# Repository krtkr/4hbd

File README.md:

# 4hbd
4 Halfbridge Driver board schematics and PCB files, KiCAD

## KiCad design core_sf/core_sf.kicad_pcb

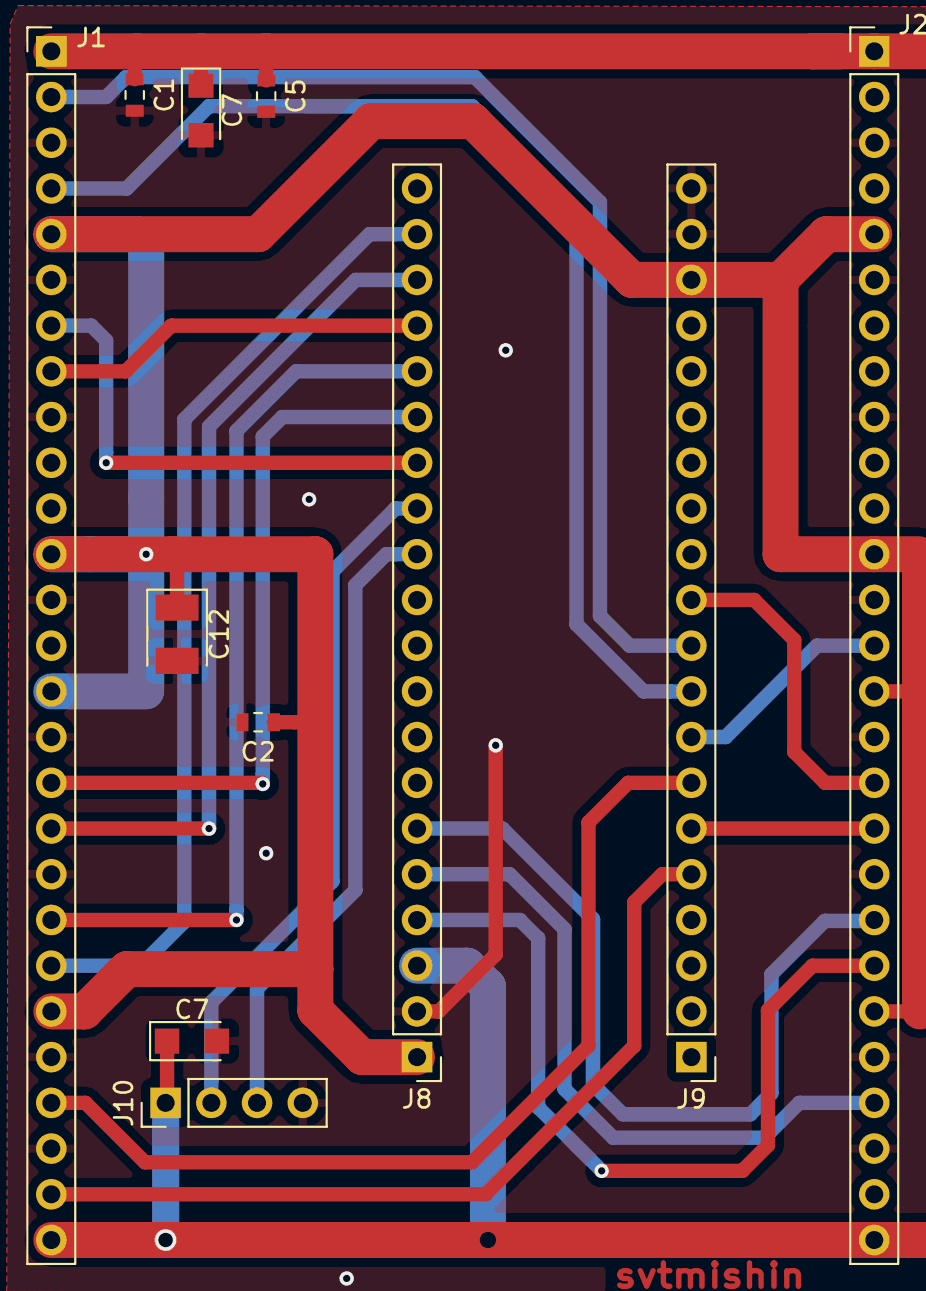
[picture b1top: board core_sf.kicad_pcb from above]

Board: 2 copper layers, 11 parts (0 on the bottom side), 21 nets.

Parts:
C1: 470pF; C_0603_1608Metric
C2, C5: 0.1uF; C_0603_1608Metric
C7, C7#2: 22uF 6.3V; CP_EIA-3216-18_Kemet-A
C12: 220uF 4V; CP_EIA-3528-21_Kemet-B
J1, J2: Conn_01x27; PinHeader_1x27_P2.54mm_Vertical
J8, J9: Conn_01x20; PinHeader_1x20_P2.54mm_Vertical
J10: Conn_01x04; PinHeader_1x04_P2.54mm_Vertical

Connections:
+3V3: C2.1, C12.1, J1.5, J1.12, J1.15, J1.22, J2.5, J2.12, J2.15, J2.22, J8.1, J9.18
+5V: C1.1, C5.1, C7.1, C7#2.1, J1.1, J1.27, J2.1, J2.27, J8.3, J10.1
/ADC1_IN0: J1.4, J9.9
/ADC1_IN3: J2.14, J9.8
/ADC1_IN4: J1.24, J9.7
/ADC2_IN9: J1.26, J9.5
/ADC3_IN10: J1.2, J9.10
/TIM1_CH1: J1.20, J8.16
/TIM1_CH1N: J1.21, J8.19
/TIM1_CH2: J1.17, J8.15
/TIM1_CH2N: J1.18, J8.18
/TIM1_CH4: J1.7, J8.14
/TIM1_CH4N: J1.8, J8.17
/TIM2_FAN_PULSE: J2.18, J9.6
/TIM3_FAN_PWM: J2.17, J9.11
/TIM4_ENC_A: J2.21, J8.4
/TIM4_ENC_B: J2.24, J8.5
/TIM4_ENC_Z: J2.20, J8.6
/canRX: J8.13, J10.2
/canTx: J8.12, J10.3
GND: C1.2, C2.2, C5.2, C7.2, C7#2.2, C12.2, J1.3, J1.6, J1.9, J1.13, J1.16, J1.19, J1.23, J1.25, J2.3, J2.6, J2.9, J2.13, J2.16, J2.19, J2.23, J2.25, J8.2, J9.19, J9.20, J10.4

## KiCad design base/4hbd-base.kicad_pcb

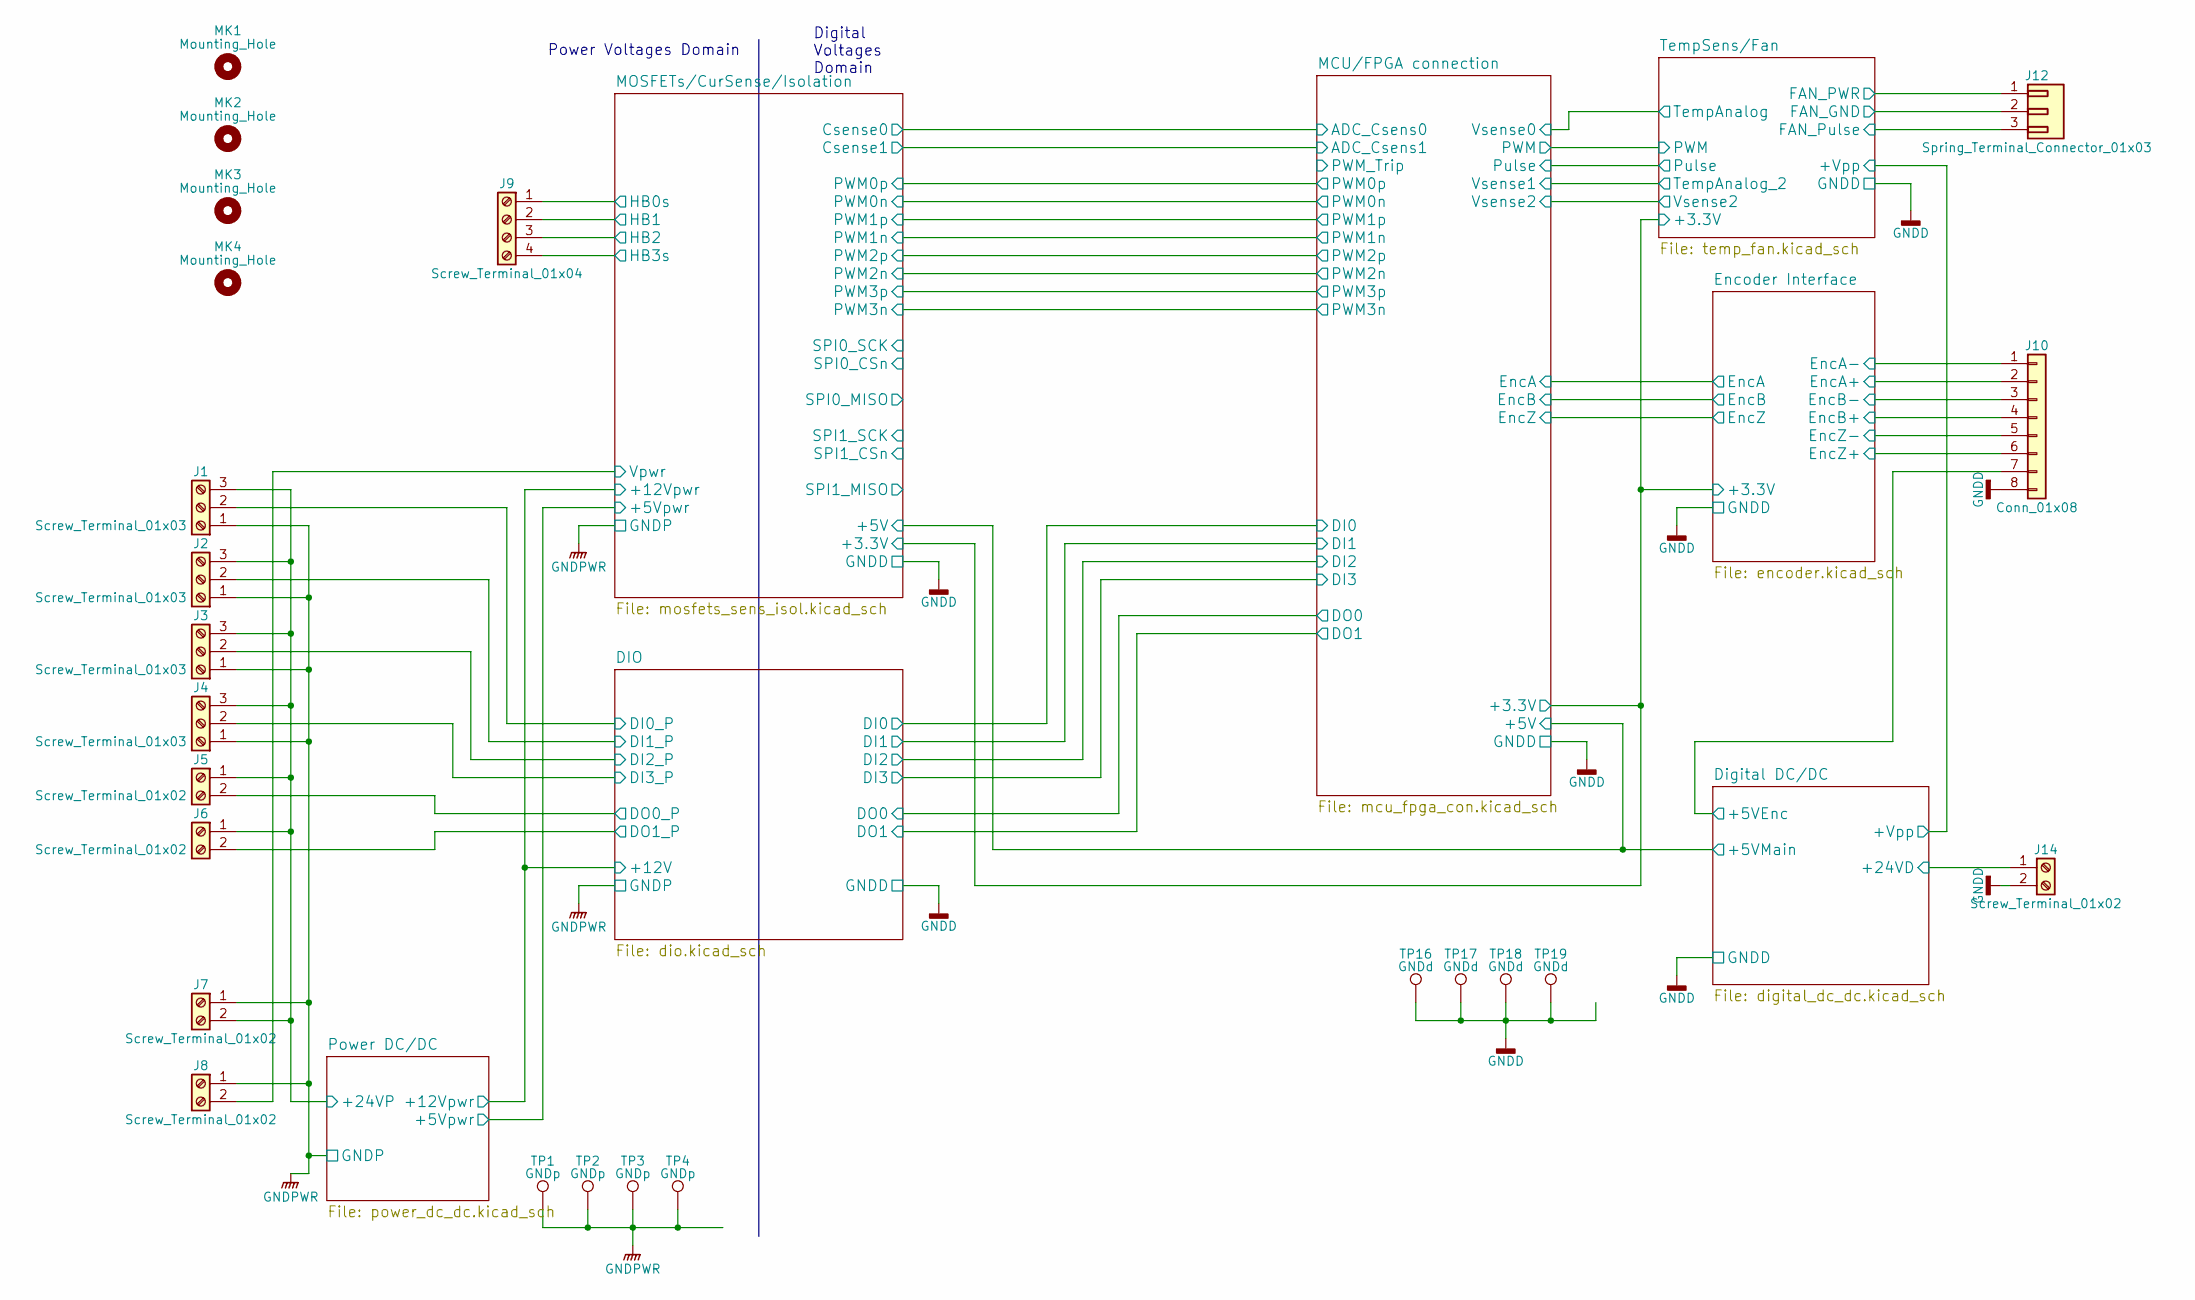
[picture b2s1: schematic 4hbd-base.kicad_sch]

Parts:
J1, J2, J3, J4: Screw_Terminal_01x03; TerminalBlock_Altech_AK300-3_P5.00mm
J5, J6, J7, J8, J14: Screw_Terminal_01x02; TerminalBlock_Altech_AK300-2_P5.00mm
J9: Screw_Terminal_01x04; TerminalBlock_Altech_AK300-4_P5.00mm
J10: Conn_01x08; PinHeader_1x08_P2.54mm_Horizontal
J12: Spring_Terminal_Connector_01x03; PinHeader_1x03_P2.54mm_Vertical
MK1, MK2, MK3, MK4: Mounting_Hole; MountingHole_3.5mm
TP1, TP2, TP3, TP4: GNDp; TestPoint_Pad_D1.5mm
TP16, TP17, TP18, TP19: GNDd; TestPoint_Pad_D1.5mm

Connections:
/DIO/DI0_P: J1.2; also elsewhere on the board
/DIO/DI1_P: J2.2; also elsewhere on the board
/DIO/DI2_P: J3.2; also elsewhere on the board
/DIO/DI3_P: J4.2; also elsewhere on the board
/DIO/DO0_P: J5.2; also elsewhere on the board
/DIO/DO1_P: J6.2; also elsewhere on the board
/Digital DC/DC/+5VEnc: J10.7; also elsewhere on the board
/Digital DC/DC/+24VD: J14.1; also elsewhere on the board
/Encoder Interface/EncA+: J10.2; also elsewhere on the board
/Encoder Interface/EncA-: J10.1; also elsewhere on the board
/Encoder Interface/EncB+: J10.4; also elsewhere on the board
/Encoder Interface/EncB-: J10.3; also elsewhere on the board
/Encoder Interface/EncZ+: J10.6; also elsewhere on the board
/Encoder Interface/EncZ-: J10.5; also elsewhere on the board
/MOSFETs/CurSense/Isolation/HB0s: J9.1; also elsewhere on the board
/MOSFETs/CurSense/Isolation/HB1: J9.2; also elsewhere on the board
/MOSFETs/CurSense/Isolation/HB2: J9.3; also elsewhere on the board
/MOSFETs/CurSense/Isolation/HB3s: J9.4; also elsewhere on the board
/MOSFETs/CurSense/Isolation/Vpwr: J8.2; also elsewhere on the board
/Power DC/DC/+24VP: J1.3, J2.3, J3.3, J4.3, J5.1, J6.1, J7.2; also elsewhere on the board
/TempSens/Fan/FAN_PULSE: J12.3; also elsewhere on the board
/TempSens/Fan/FAN_PWR: J12.1; also elsewhere on the board
GND: J10.8, J12.2, J14.2, TP16.1, TP17.1, TP18.1, TP19.1; also elsewhere on the board
GNDPWR: J1.1, J2.1, J3.1, J4.1, J7.1, J8.1, TP1.1, TP2.1, TP3.1, TP4.1; also elsewhere on the board

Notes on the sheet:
Power Voltages Domain
Digital Voltages Domain

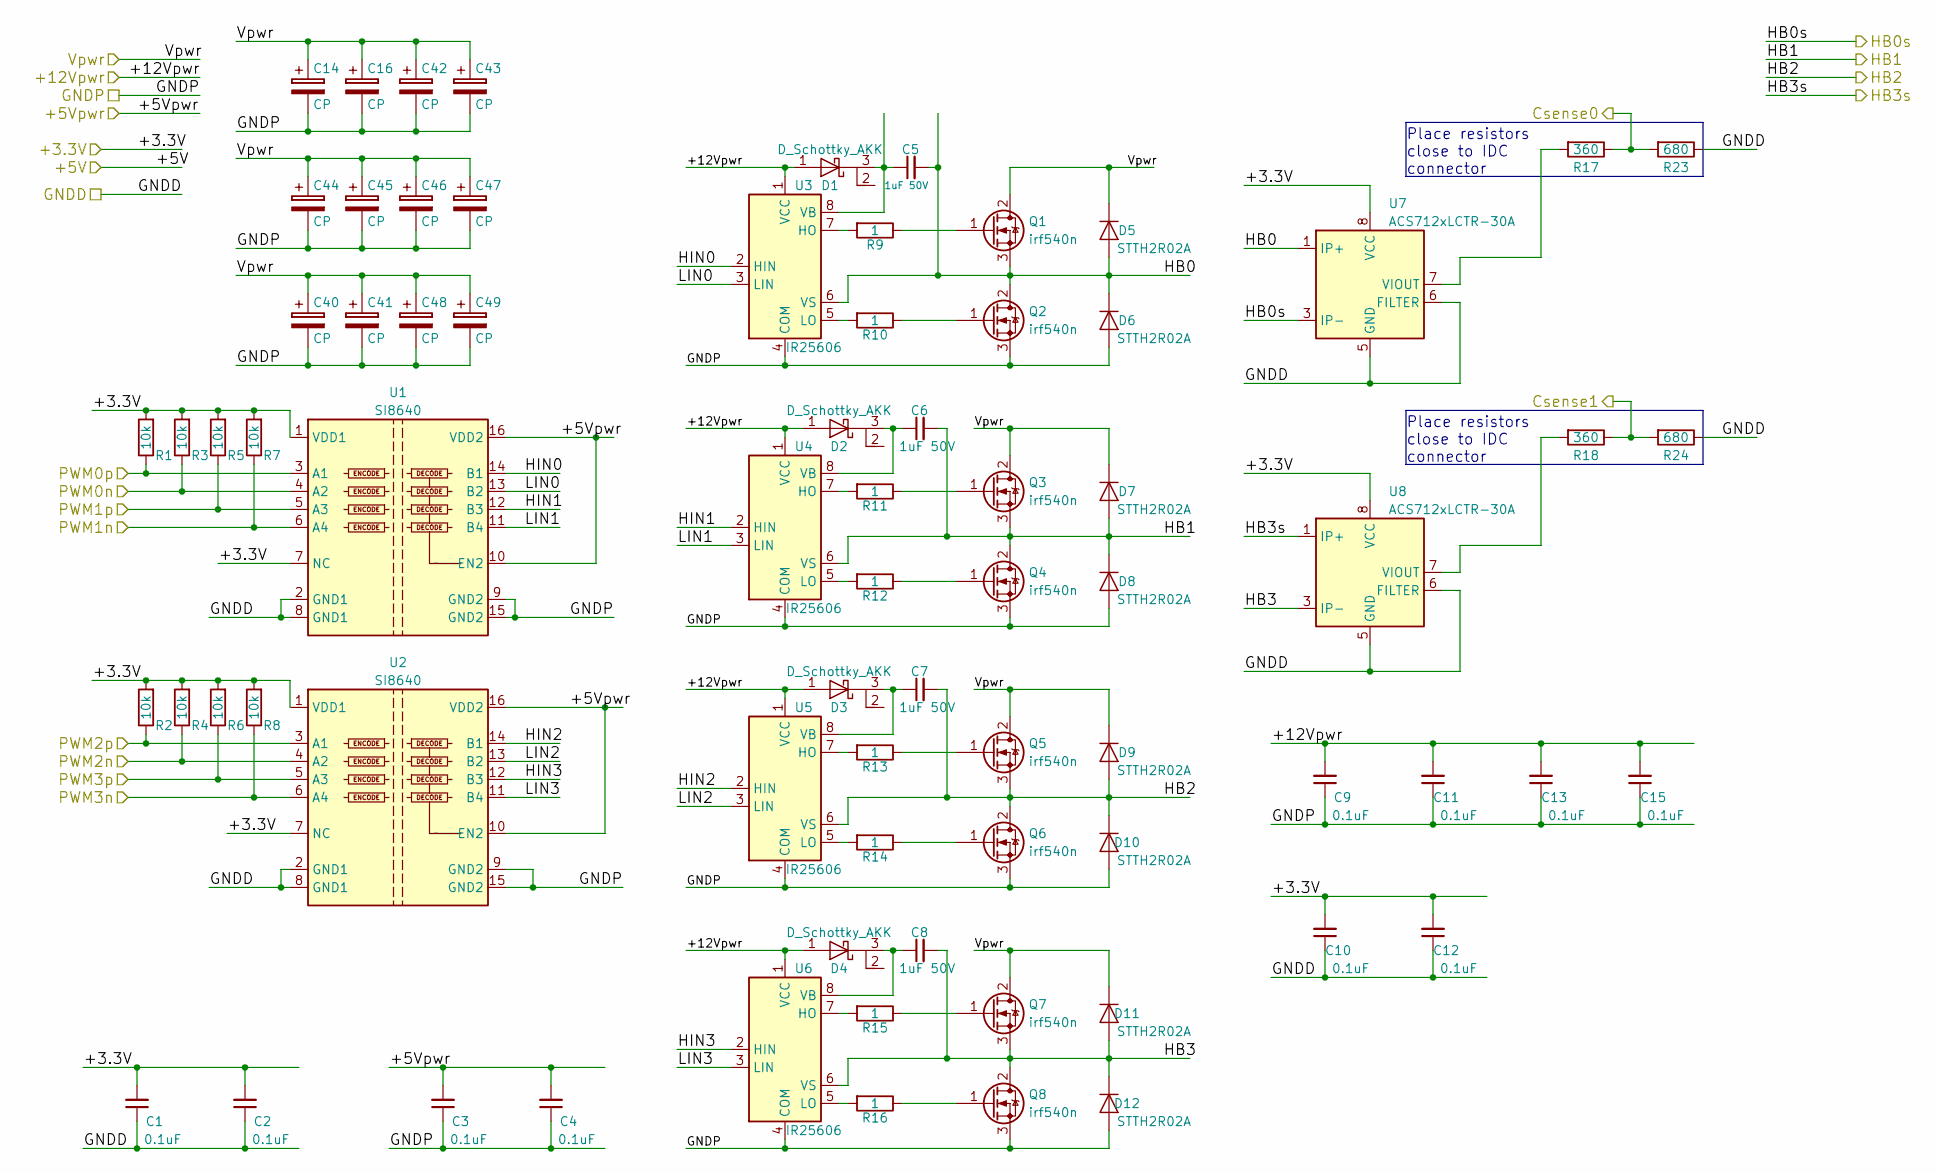
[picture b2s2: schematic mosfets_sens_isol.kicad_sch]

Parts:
C1, C2, C3, C4, C9, C10, C11, C12, C13, C15: 0.1uF; C_0603_1608Metric
C5, C6, C7, C8: 1uF 50V; C_0805_2012Metric
C14, C16: CP; CP_Radial_D22.0mm_P10.00mm_SnapIn
C40, C41, C48, C49: CP; CP_Radial_D10.0mm_P5.00mm
C42, C43: CP; CP_Radial_D12.5mm_P5.00mm
C44, C45, C46, C47: CP; C_2220_5650Metric_Pad2.02x5.50mm_HandSolder
D1, D2, D3, D4: D_Schottky_AKK; SOT-23
D5, D6, D7, D8, D9, D10, D11, D12: STTH2R02A; D_SMA
Q1, Q2, Q3, Q4, Q5, Q6, Q7, Q8: irf540n; TO-220-3_TabUp
R1, R2, R3, R4, R5, R6, R7, R8: 10k; R_0603_1608Metric
R9, R10, R11, R12, R13, R14, R15, R16: 1; R_0603_1608Metric
R17, R18: 360; R_0603_1608Metric
R23, R24: 680; R_0603_1608Metric
U1, U2: SI8640; SOIC-16_3.9x9.9mm_P1.27mm
U3, U4, U5, U6: IR25606; SOIC-8_3.9x4.9mm_P1.27mm
U7, U8: ACS712xLCTR-30A; SOIC-8_3.9x4.9mm_P1.27mm

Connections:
/DIO/+12V: C9.2, C11.2, C13.2, C15.2, D1.1 (A), D2.1 (A), D3.1 (A), D4.1 (A), U3.1 (VCC), U4.1 (VCC), U5.1 (VCC), U6.1 (VCC); also elsewhere on the board
/Encoder Interface/+3.3V: C1.2, C2.2, C10.2, C12.2, R1.2, R2.2, R3.2, R4.2, R5.2, R6.2, R7.2, R8.2, U1.1 (VDD1), U1.7 (NC), U2.1 (VDD1), U2.7 (NC), U7.8 (VCC), U8.8 (VCC); also elsewhere on the board
/MCU/FPGA connection/ADC_Csens0: R17.1, R23.2; also elsewhere on the board
/MCU/FPGA connection/ADC_Csens1: R18.1, R24.2; also elsewhere on the board
/MCU/FPGA connection/PWM0n: R3.1, U1.4 (A2); also elsewhere on the board
/MCU/FPGA connection/PWM0p: R1.1, U1.3 (A1); also elsewhere on the board
/MCU/FPGA connection/PWM1n: R7.1, U1.6 (A4); also elsewhere on the board
/MCU/FPGA connection/PWM1p: R5.1, U1.5 (A3); also elsewhere on the board
/MCU/FPGA connection/PWM2n: R4.1, U2.4 (A2); also elsewhere on the board
/MCU/FPGA connection/PWM2p: R2.1, U2.3 (A1); also elsewhere on the board
/MCU/FPGA connection/PWM3n: R8.1, U2.6 (A4); also elsewhere on the board
/MCU/FPGA connection/PWM3p: R6.1, U2.5 (A3); also elsewhere on the board
/MOSFETs/CurSense/Isolation/+5Vpwr: C3.2, C4.2, U1.10 (EN2), U1.16 (VDD2), U2.10 (EN2), U2.16 (VDD2); also elsewhere on the board
/MOSFETs/CurSense/Isolation/HB0: C5.2, D5.2 (A), D6.1 (K), Q1.3 (S), Q2.2 (D), U3.6 (VS), U7.1 (IP+), U7.2 (IP+)
/MOSFETs/CurSense/Isolation/HB0s: U7.3 (IP-), U7.4 (IP-); also elsewhere on the board
/MOSFETs/CurSense/Isolation/HB1: C6.2, D7.2 (A), D8.1 (K), Q3.3 (S), Q4.2 (D), U4.6 (VS); also elsewhere on the board
/MOSFETs/CurSense/Isolation/HB2: C7.2, D9.2 (A), D10.1 (K), Q5.3 (S), Q6.2 (D), U5.6 (VS); also elsewhere on the board
/MOSFETs/CurSense/Isolation/HB3: C8.2, D11.2 (A), D12.1 (K), Q7.3 (S), Q8.2 (D), U6.6 (VS), U8.3 (IP-), U8.4 (IP-)
/MOSFETs/CurSense/Isolation/HB3s: U8.1 (IP+), U8.2 (IP+); also elsewhere on the board
/MOSFETs/CurSense/Isolation/HIN0: U1.14 (B1), U3.2 (HIN)
/MOSFETs/CurSense/Isolation/HIN1: U1.12 (B3), U4.2 (HIN)
/MOSFETs/CurSense/Isolation/HIN2: U2.14 (B1), U5.2 (HIN)
/MOSFETs/CurSense/Isolation/HIN3: U2.12 (B3), U6.2 (HIN)
/MOSFETs/CurSense/Isolation/LIN0: U1.13 (B2), U3.3 (LIN)
/MOSFETs/CurSense/Isolation/LIN1: U1.11 (B4), U4.3 (LIN)
/MOSFETs/CurSense/Isolation/LIN2: U2.13 (B2), U5.3 (LIN)
/MOSFETs/CurSense/Isolation/LIN3: U2.11 (B4), U6.3 (LIN)
/MOSFETs/CurSense/Isolation/Vpwr: C14.1, C16.1, C40.1, C41.1, C42.1, C43.1, C44.1, C45.1, C46.1, C47.1, C48.1, C49.1, D5.1 (K), D7.1 (K), D9.1 (K), D11.1 (K), Q1.2 (D), Q3.2 (D), Q5.2 (D), Q7.2 (D); also elsewhere on the board
GND: C1.1, C2.1, C10.1, C12.1, R23.1, R24.1, U1.2 (GND1), U1.8 (GND1), U2.2 (GND1), U2.8 (GND1), U7.5 (GND), U7.6 (FILTER), U8.5 (GND), U8.6 (FILTER); also elsewhere on the board
GNDPWR: C3.1, C4.1, C9.1, C11.1, C13.1, C14.2, C15.1, C16.2, C40.2, C41.2, C42.2, C43.2, C44.2, C45.2, C46.2, C47.2, C48.2, C49.2, D6.2 (A), D8.2 (A), D10.2 (A), D12.2 (A), Q2.3 (S), Q4.3 (S), Q6.3 (S), Q8.3 (S), U1.9 (GND2), U1.15 (GND2), U2.9 (GND2), U2.15 (GND2), U3.4 (COM), U4.4 (COM), U5.4 (COM), U6.4 (COM); also elsewhere on the board
unnamed: C5.1, D1.3 (K), U3.8 (VB)
unnamed: C6.1, D2.3 (K), U4.8 (VB)
unnamed: C7.1, D3.3 (K), U5.8 (VB)
unnamed: C8.1, D4.3 (K), U6.8 (VB)
unnamed: Q1.1 (G), R9.1
unnamed: Q2.1 (G), R10.1
unnamed: Q3.1 (G), R11.1
unnamed: Q4.1 (G), R12.1
unnamed: Q5.1 (G), R13.1
unnamed: Q6.1 (G), R14.1
unnamed: Q7.1 (G), R15.1
unnamed: Q8.1 (G), R16.1
unnamed: R9.2, U3.7 (HO)
unnamed: R10.2, U3.5 (LO)
unnamed: R11.2, U4.7 (HO)
unnamed: R12.2, U4.5 (LO)
unnamed: R13.2, U5.7 (HO)
unnamed: R14.2, U5.5 (LO)
unnamed: R15.2, U6.7 (HO)
unnamed: R16.2, U6.5 (LO)
unnamed: R17.2, U7.7 (VIOUT)
unnamed: R18.2, U8.7 (VIOUT)

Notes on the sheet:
Place resistors close to IDC connector

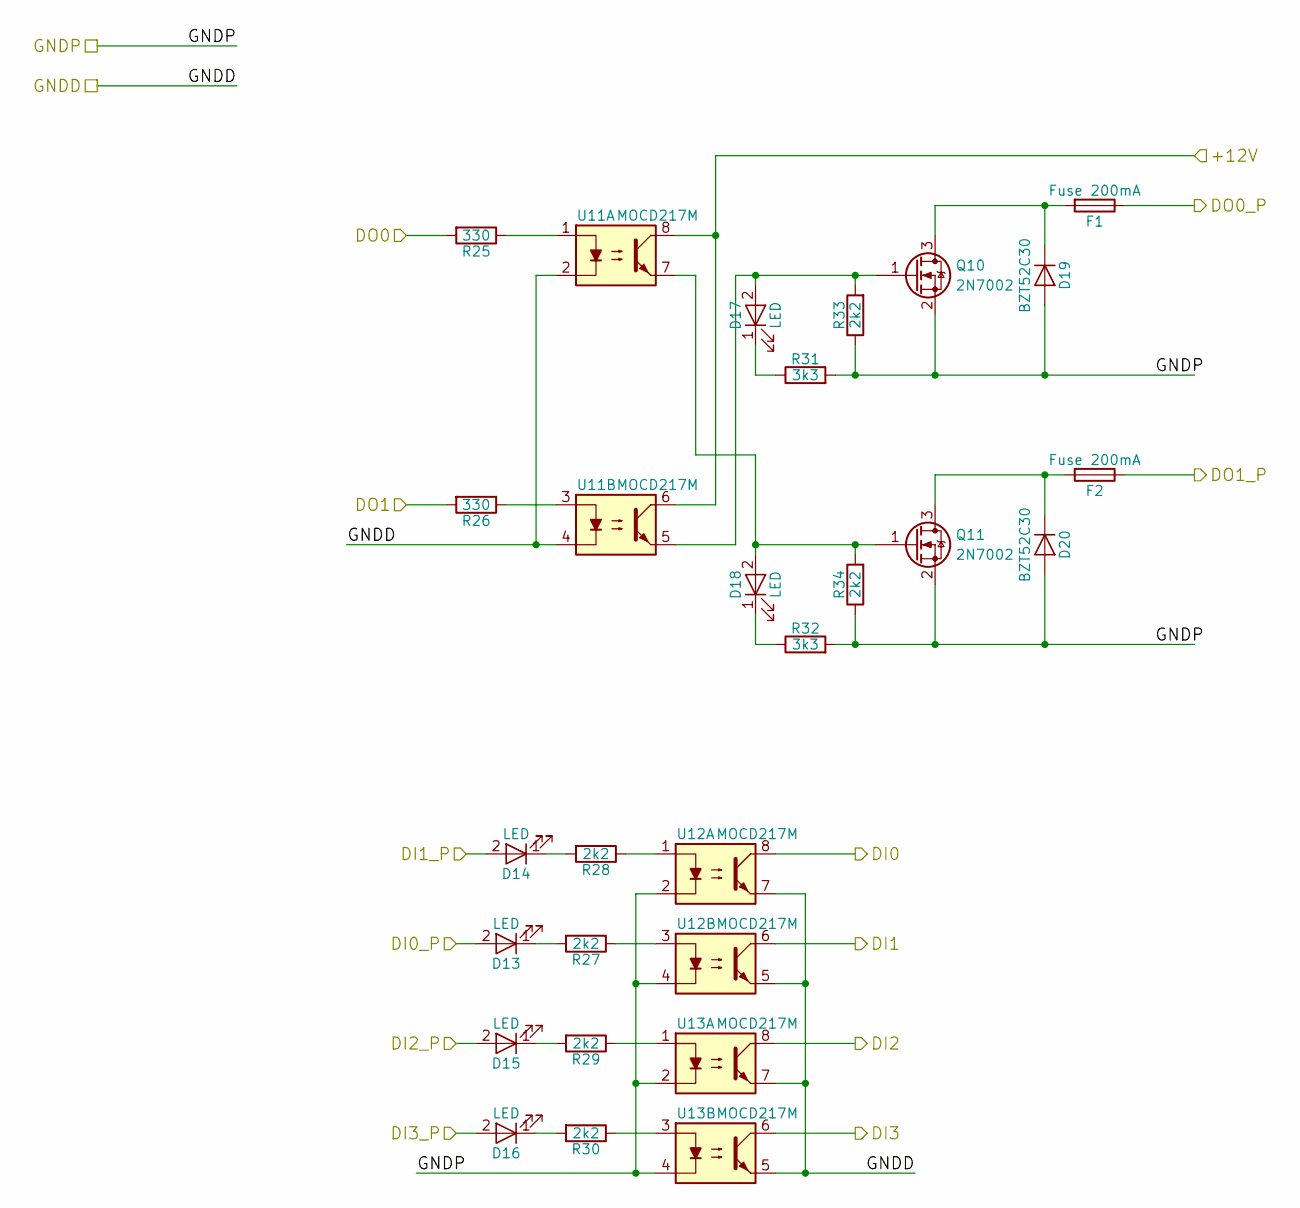
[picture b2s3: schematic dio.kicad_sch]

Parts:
D13, D14, D15, D16, D17, D18: LED; LED_0603_1608Metric_ReverseMount
D19, D20: BZT52C30; D_SOD-123
F1, F2: Fuse 200mA; Fuse_1206_3216Metric
Q10, Q11: 2N7002; SOT-23
R25, R26: 330; R_0603_1608Metric
R27, R28, R29, R30, R33, R34: 2k2; R_0603_1608Metric
R31, R32: 3k3; R_0603_1608Metric
U11, U12, U13: MOCD217M; SOIC-8_3.9x4.9mm_P1.27mm

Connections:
/DIO/+12V: U11.6, U11.8; also elsewhere on the board
/DIO/DI0: U12.8; also elsewhere on the board
/DIO/DI0_P: D13.2 (A); also elsewhere on the board
/DIO/DI1: U12.6; also elsewhere on the board
/DIO/DI1_P: D14.2 (A); also elsewhere on the board
/DIO/DI2: U13.8; also elsewhere on the board
/DIO/DI2_P: D15.2 (A); also elsewhere on the board
/DIO/DI3: U13.6; also elsewhere on the board
/DIO/DI3_P: D16.2 (A); also elsewhere on the board
/DIO/DO0: R25.2; also elsewhere on the board
/DIO/DO0_P: F1.1; also elsewhere on the board
/DIO/DO1: R26.2; also elsewhere on the board
/DIO/DO1_P: F2.1; also elsewhere on the board
GND: U11.2, U11.4, U12.5, U12.7, U13.5, U13.7; also elsewhere on the board
GNDPWR: D19.2 (A), D20.2 (A), Q10.2 (S), Q11.2 (S), R31.2, R32.2, R33.1, R34.1, U12.2, U12.4, U13.2, U13.4; also elsewhere on the board
unnamed: D13.1 (K), R27.2
unnamed: D14.1 (K), R28.2
unnamed: D15.1 (K), R29.2
unnamed: D16.1 (K), R30.2
unnamed: D17.1 (K), R31.1
unnamed: D17.2 (A), Q10.1 (G), R33.2, U11.5
unnamed: D18.1 (K), R32.1
unnamed: D18.2 (A), Q11.1 (G), R34.2, U11.7
unnamed: D19.1 (K), F1.2, Q10.3 (D)
unnamed: D20.1 (K), F2.2, Q11.3 (D)
unnamed: R25.1, U11.1
unnamed: R26.1, U11.3
unnamed: R27.1, U12.3
unnamed: R28.1, U12.1
unnamed: R29.1, U13.1
unnamed: R30.1, U13.3

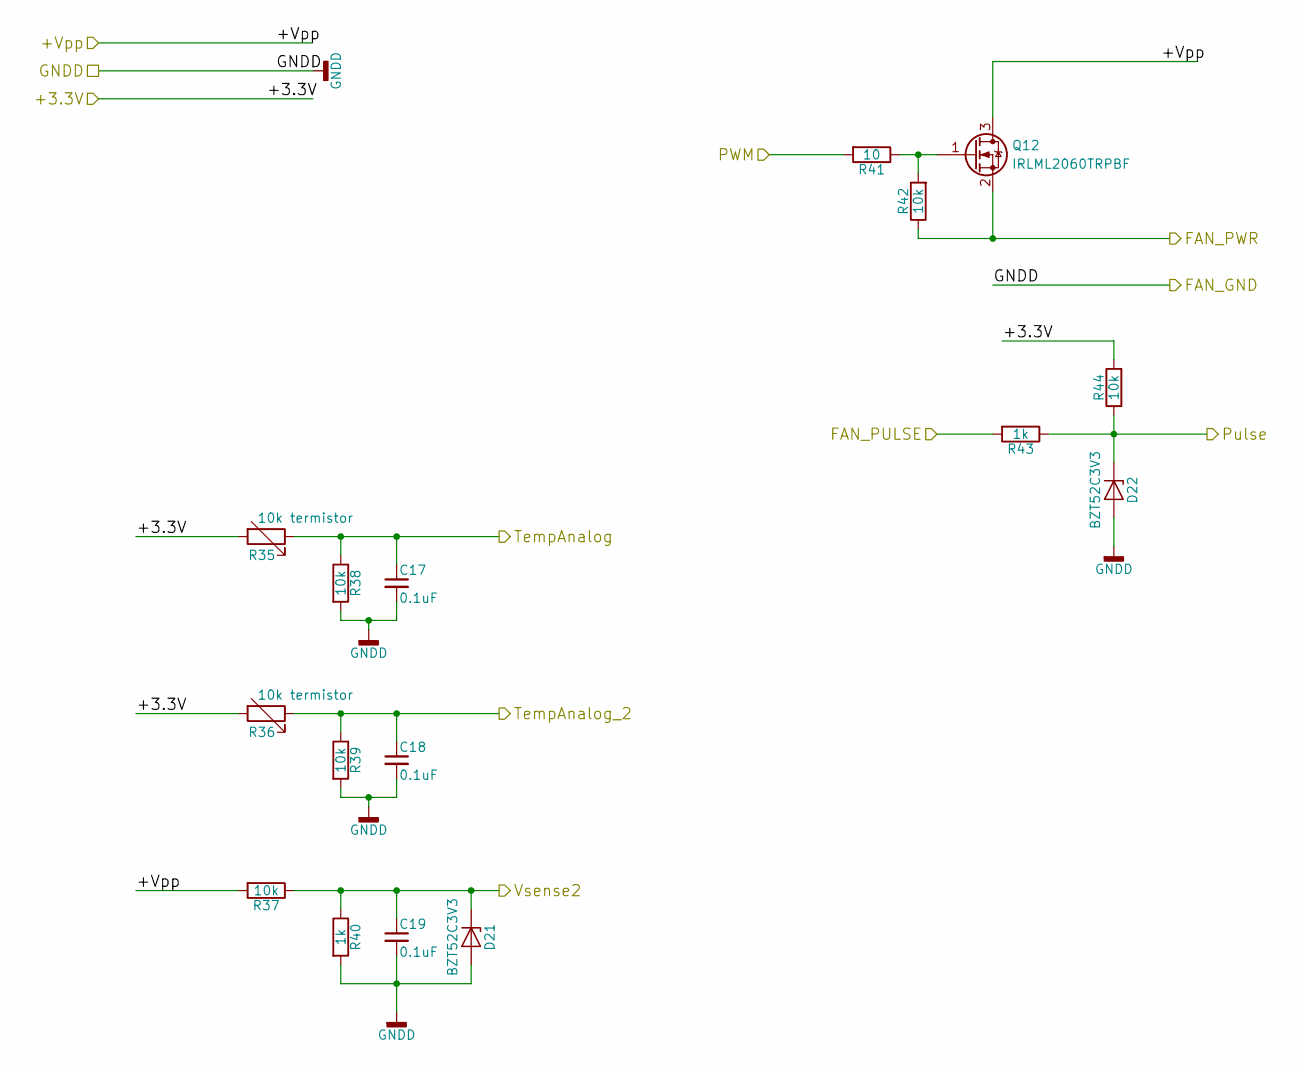
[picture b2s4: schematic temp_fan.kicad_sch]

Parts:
C17, C18, C19: 0.1uF; C_0805_2012Metric
D21, D22: BZT52C3V3; D_SOD-123
Q12: IRLML2060TRPBF; SOT-23
R35, R36: 10k termistor; R_0805_2012Metric
R37, R38, R39, R42, R44: 10k; R_0603_1608Metric
R40, R43: 1k; R_0603_1608Metric
R41: 10; R_0603_1608Metric

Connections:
/Digital DC/DC/+Vpp: Q12.3 (D), R37.2; also elsewhere on the board
/Encoder Interface/+3.3V: R35.2, R36.2, R44.2; also elsewhere on the board
/MCU/FPGA connection/PWM: R41.2; also elsewhere on the board
/MCU/FPGA connection/Pulse: D22.1 (K), R43.1, R44.1; also elsewhere on the board
/MCU/FPGA connection/Vsense2: C19.1, D21.1 (K), R37.1, R40.1; also elsewhere on the board
/TempSens/Fan/FAN_PULSE: R43.2; also elsewhere on the board
/TempSens/Fan/FAN_PWR: Q12.2 (S), R42.1; also elsewhere on the board
/TempSens/Fan/TempAnalog: C17.1, R35.1, R38.1; also elsewhere on the board
/TempSens/Fan/TempAnalog_2: C18.1, R36.1, R39.1; also elsewhere on the board
GND: C17.2, C18.2, C19.2, D21.2 (A), D22.2 (A), R38.2, R39.2, R40.2; also elsewhere on the board
unnamed: Q12.1 (G), R41.1, R42.2

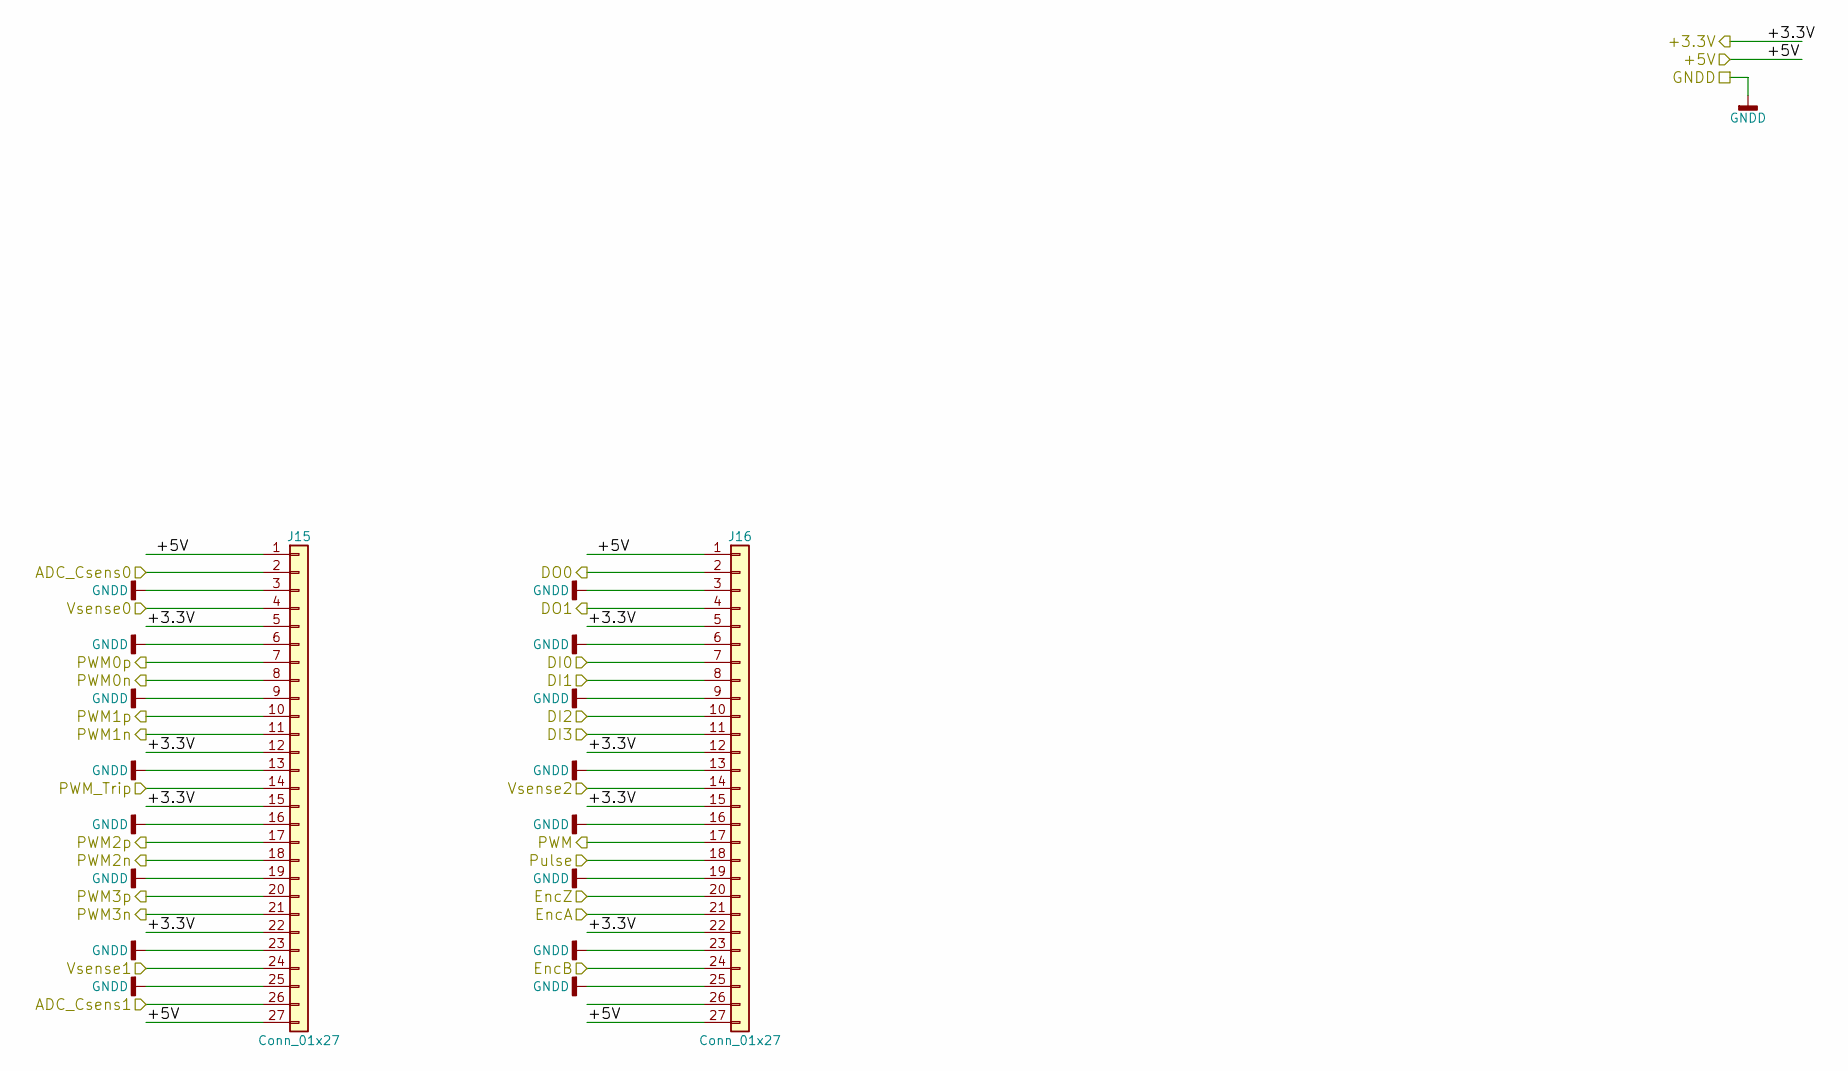
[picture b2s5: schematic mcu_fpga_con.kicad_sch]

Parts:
J15, J16: Conn_01x27; PinHeader_1x27_P2.54mm_Vertical

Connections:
/DIO/DI0: J16.7; also elsewhere on the board
/DIO/DI1: J16.8; also elsewhere on the board
/DIO/DI2: J16.10; also elsewhere on the board
/DIO/DI3: J16.11; also elsewhere on the board
/DIO/DO0: J16.2; also elsewhere on the board
/DIO/DO1: J16.4; also elsewhere on the board
/Encoder Interface/+3.3V: J15.5, J15.12, J15.15, J15.22, J16.5, J16.12, J16.15, J16.22; also elsewhere on the board
/Encoder Interface/EncA: J16.21; also elsewhere on the board
/Encoder Interface/EncB: J16.24; also elsewhere on the board
/Encoder Interface/EncZ: J16.20; also elsewhere on the board
/MCU/FPGA connection/+5V: J15.1, J15.27, J16.1, J16.27; also elsewhere on the board
/MCU/FPGA connection/ADC_Csens0: J15.2; also elsewhere on the board
/MCU/FPGA connection/ADC_Csens1: J15.26; also elsewhere on the board
/MCU/FPGA connection/PWM: J16.17; also elsewhere on the board
/MCU/FPGA connection/PWM0n: J15.8; also elsewhere on the board
/MCU/FPGA connection/PWM0p: J15.7; also elsewhere on the board
/MCU/FPGA connection/PWM1n: J15.11; also elsewhere on the board
/MCU/FPGA connection/PWM1p: J15.10; also elsewhere on the board
/MCU/FPGA connection/PWM2n: J15.18; also elsewhere on the board
/MCU/FPGA connection/PWM2p: J15.17; also elsewhere on the board
/MCU/FPGA connection/PWM3n: J15.21; also elsewhere on the board
/MCU/FPGA connection/PWM3p: J15.20; also elsewhere on the board
/MCU/FPGA connection/Pulse: J16.18; also elsewhere on the board
/MCU/FPGA connection/Vsense2: J16.14; also elsewhere on the board
/TempSens/Fan/TempAnalog: J15.4; also elsewhere on the board
/TempSens/Fan/TempAnalog_2: J15.24; also elsewhere on the board
GND: J15.3, J15.6, J15.9, J15.13, J15.16, J15.19, J15.23, J15.25, J16.3, J16.6, J16.9, J16.13, J16.16, J16.19, J16.23, J16.25; also elsewhere on the board

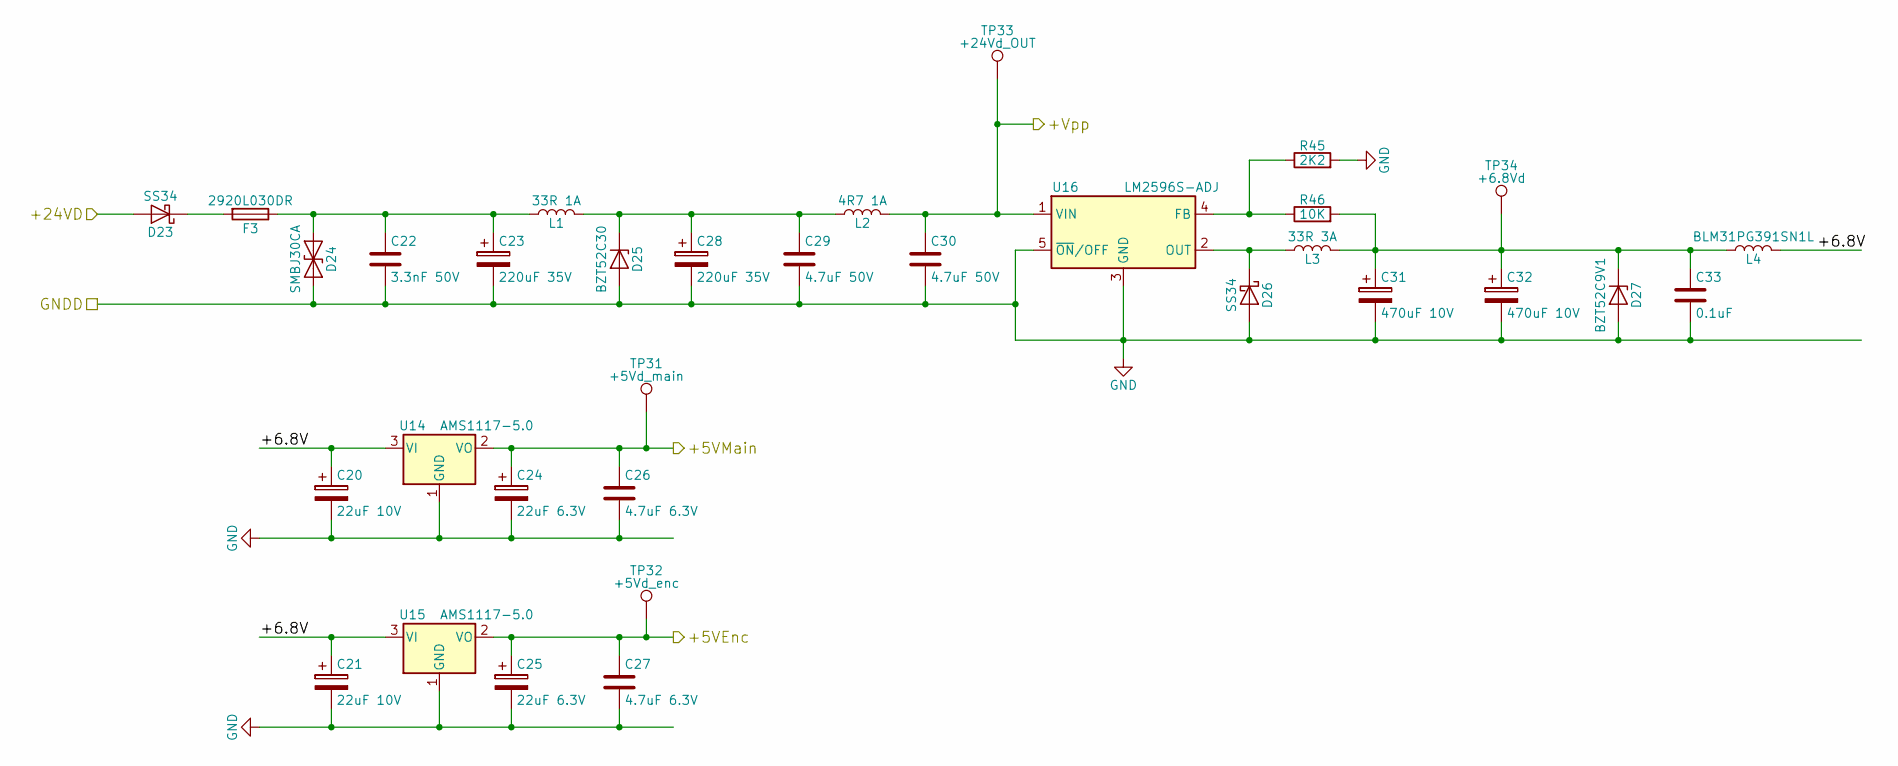
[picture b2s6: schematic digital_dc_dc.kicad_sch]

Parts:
C20, C21: 22uF 10V; CP_EIA-3216-18_Kemet-A
C22: 3.3nF 50V; C_0603_1608Metric
C23, C28: 220uF 35V; CP_Elec_8x10
C24, C25: 22uF 6.3V; CP_EIA-3216-18_Kemet-A
C26, C27: 4.7uF 6.3V; C_0603_1608Metric
C29, C30: 4.7uF 50V; C_1210_3225Metric
C31, C32: 470uF 10V; CP_Elec_8x10
C33: 0.1uF; C_0603_1608Metric
D23, D26: SS34; D_SMA
D24: SMBJ30CA; D_SMB
D25: BZT52C30; D_SOD-123
D27: BZT52C9V1; D_SOD-123
F3: 2920L030DR; Fuse_2920_7451Metric
L1: 33R 1A; L_7.3x7.3_H3.5
L2: 4R7 1A; L_Taiyo-Yuden_MD-3030
L3: 33R 3A; L_12x12mm_h8mm
L4: BLM31PG391SN1L; L_1206_3216Metric
R45: 2K2; R_0603_1608Metric
R46: 10K; R_0603_1608Metric
TP31: +5Vd_main; TestPoint_Pad_D1.5mm
TP32: +5Vd_enc; TestPoint_Pad_D1.5mm
TP33: +24Vd_OUT; TestPoint_Pad_D1.5mm
TP34: +6.8Vd; TestPoint_Pad_D1.5mm
U14, U15: AMS1117-5.0; SOT-223
U16: LM2596S-ADJ; TO-263-5_TabPin3

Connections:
/Digital DC/DC/+5VEnc: C25.1, C27.1, TP32.1, U15.2 (VO), U15.4; also elsewhere on the board
/Digital DC/DC/+6.8V: C20.1, C21.1, L4.2, U14.3 (VI), U15.3 (VI)
/Digital DC/DC/+24VD: D23.2 (A); also elsewhere on the board
/Digital DC/DC/+Vpp: C30.1, L2.2, TP33.1, U16.1 (VIN); also elsewhere on the board
/MCU/FPGA connection/+5V: C24.1, C26.1, TP31.1, U14.2 (VO), U14.4; also elsewhere on the board
GND: C20.2, C21.2, C22.2, C23.2, C24.2, C25.2, C26.2, C27.2, C28.2, C29.2, C30.2, C31.2, C32.2, C33.2, D24.2 (A2), D25.2 (A), D26.2 (A), D27.2 (A), R45.2, U14.1 (GND), U15.1 (GND), U16.3 (GND), U16.5 (~ON/OFF); also elsewhere on the board
unnamed: C22.1, C23.1, D24.1 (A1), F3.1, L1.1
unnamed: C28.1, C29.1, D25.1 (K), L1.2, L2.1
unnamed: C31.1, C32.1, C33.1, D27.1 (K), L3.2, L4.1, R46.2, TP34.1
unnamed: D23.1 (K), F3.2
unnamed: D26.1 (K), L3.1, U16.2 (OUT)
unnamed: R45.1, R46.1, U16.4 (FB)

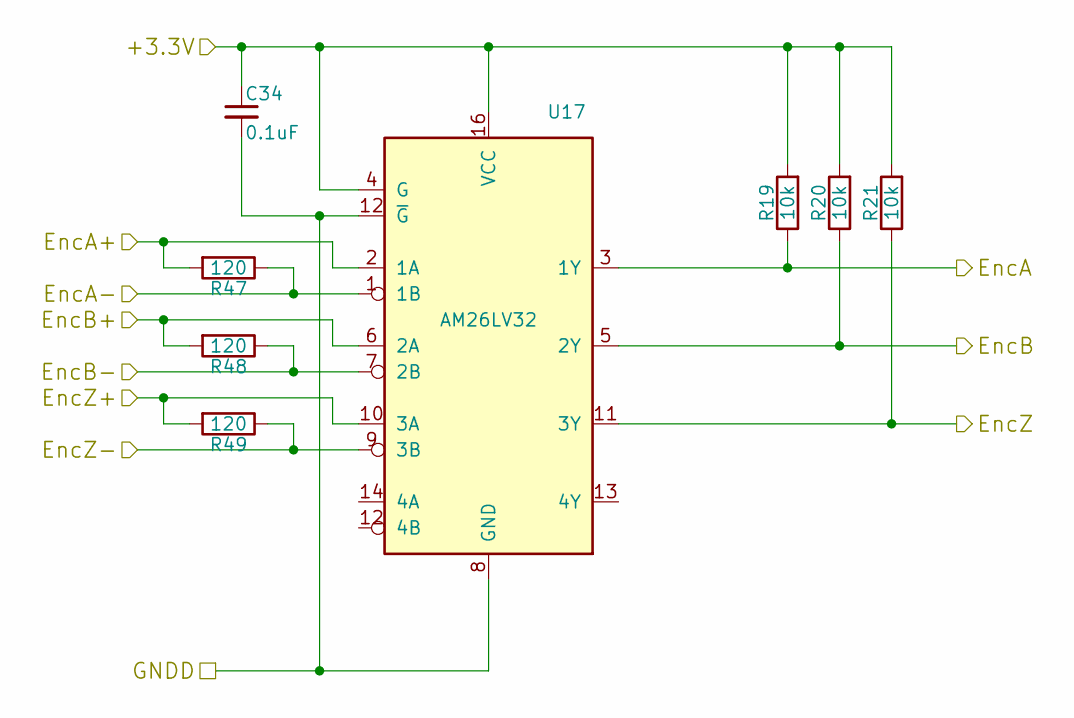
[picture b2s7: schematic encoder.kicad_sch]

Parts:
C34: 0.1uF; C_0603_1608Metric
R19, R20, R21: 10k; R_0603_1608Metric
R47, R48, R49: 120; R_0603_1608Metric
U17: AM26LV32; SOIC-16_3.9x9.9mm_P1.27mm

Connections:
/Encoder Interface/+3.3V: C34.1, R19.2, R20.2, R21.2, U17.4 (G), U17.16 (VCC); also elsewhere on the board
/Encoder Interface/EncA: R19.1, U17.3 (1Y); also elsewhere on the board
/Encoder Interface/EncA+: R47.2, U17.2 (1A); also elsewhere on the board
/Encoder Interface/EncA-: R47.1, U17.1 (1B); also elsewhere on the board
/Encoder Interface/EncB: R20.1, U17.5 (2Y); also elsewhere on the board
/Encoder Interface/EncB+: R48.2, U17.6 (2A); also elsewhere on the board
/Encoder Interface/EncB-: R48.1, U17.7 (2B); also elsewhere on the board
/Encoder Interface/EncZ: R21.1, U17.11 (3Y); also elsewhere on the board
/Encoder Interface/EncZ+: R49.2, U17.10 (3A); also elsewhere on the board
/Encoder Interface/EncZ-: R49.1, U17.9 (3B); also elsewhere on the board
GND: C34.2, U17.8 (GND), U17.12 (4B); also elsewhere on the board
